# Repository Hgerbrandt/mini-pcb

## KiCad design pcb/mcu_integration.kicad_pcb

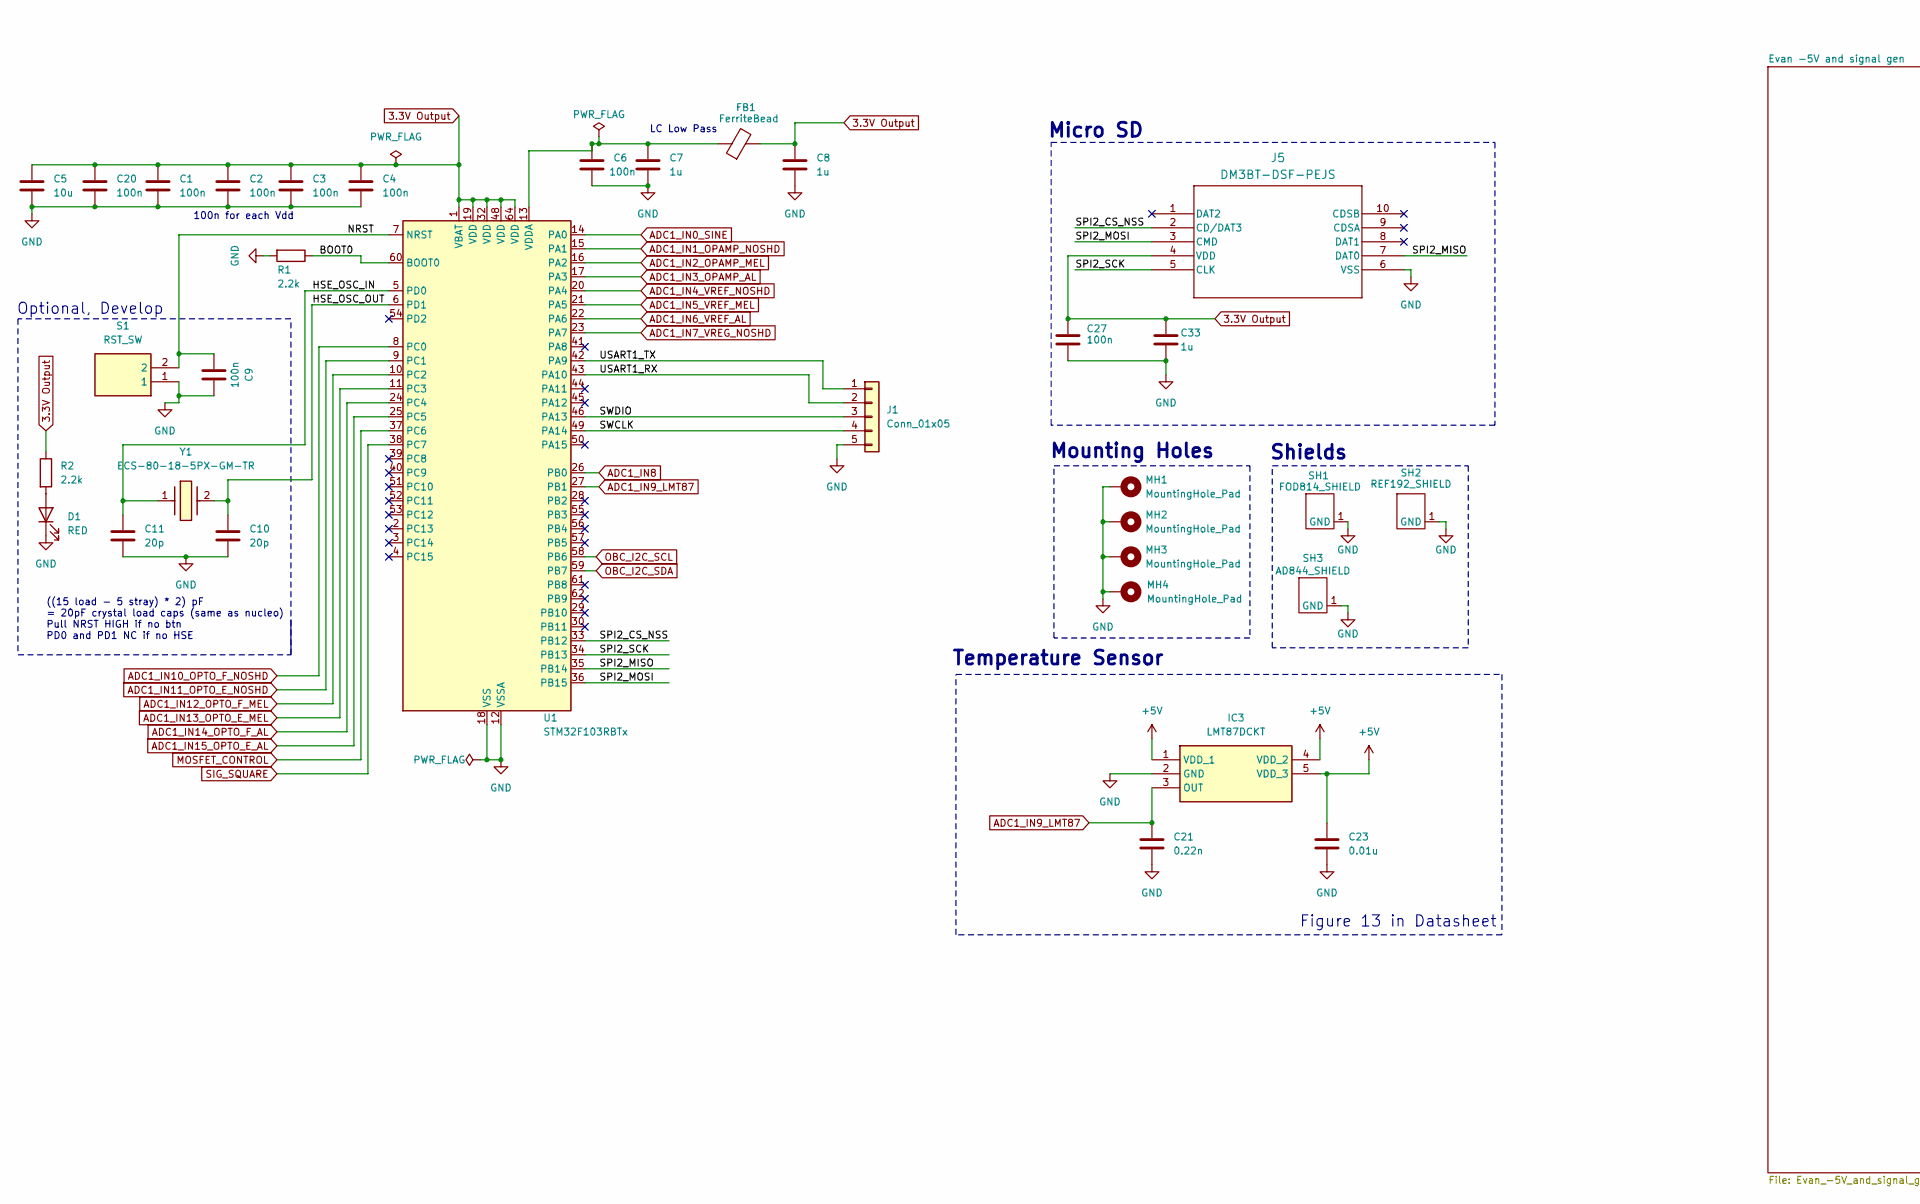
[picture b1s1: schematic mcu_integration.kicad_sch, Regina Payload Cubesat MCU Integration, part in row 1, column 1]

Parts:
C1, C2, C3, C4, C6, C9, C20, C27: 100n; C_0402_1005Metric
C5: 10u; C_0603_1608Metric
C7, C8, C33: 1u; C_0402_1005Metric
C10, C11: 20p; C_0402_1005Metric
C21: 0.22n; C_0402_1005Metric
C23: 0.01u; C_0402_1005Metric
D1: RED; LED_0603_1608Metric
FB1: FerriteBead; L_0603_1608Metric
IC3: LMT87DCKT; SOT65P210X110-5N; Mouser Part Number 595-LMT87DCKT
J1: Conn_01x05; PinHeader_1x05_P2.54mm_Vertical
J5: DM3BT-DSF-PEJS; DM3BT_DSF_PEJS
MH1, MH2, MH3, MH4: MountingHole_Pad; MountingHole_3.18mm_6.35mm_Pad
R1, R2: 2.2k; R_0402_1005Metric
S1: RST_SW; 95C04A3GWRT; Mouser Part Number 706-95C04A3GWRT
SH1: FOD814_SHIELD; FOD814 Shield
SH2: REF192_SHIELD; REF192 Shield
SH3: AD844_SHIELD; AD844 Shield
U1: STM32F103RBTx; LQFP-64_10x10mm_P0.5mm
Y1: ECS-80-18-5PX-GM-TR; ECS80185PXGMTR; Mouser Part Number 520-80-18-5PX-GM-TR

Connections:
3.3V Output: C1.1, C2.1, C3.1, C4.1, C5.1, C8.1, C20.1, C27.1, C33.1, FB1.2, J5.4 (VDD), R2.1, U1.1 (VBAT), U1.19 (VDD), U1.32 (VDD), U1.48 (VDD), U1.64 (VDD); also elsewhere on the board
+5V: C23.1, IC3.1 (VDD_1), IC3.4 (VDD_2), IC3.5 (VDD_3); also elsewhere on the board
/BOOT0: R1.1, U1.60 (BOOT0)
/HSE_OSC_IN: C11.1, U1.5 (PD0), Y1.1
/HSE_OSC_OUT: C10.1, U1.6 (PD1), Y1.2
/NRST: C9.2, S1.2, U1.7 (NRST)
/SPI2_CS_NSS: J5.2 (CD/DAT3), U1.33 (PB12)
/SPI2_MISO: J5.7 (DAT0), U1.35 (PB14)
/SPI2_MOSI: J5.3 (CMD), U1.36 (PB15)
/SPI2_SCK: J5.5 (CLK), U1.34 (PB13)
/SWCLK: J1.4, U1.49 (PA14)
/SWDIO: J1.3, U1.46 (PA13)
/USART1_RX: J1.2, U1.43 (PA10)
/USART1_TX: J1.1, U1.42 (PA9)
ADC1_IN0_SINE: U1.14 (PA0); also elsewhere on the board
ADC1_IN1_OPAMP_NOSHD: U1.15 (PA1)
ADC1_IN2_OPAMP_MEL: U1.16 (PA2)
ADC1_IN3_OPAMP_AL: U1.17 (PA3); also elsewhere on the board
ADC1_IN4_VREF_NOSHD: U1.20 (PA4)
ADC1_IN5_VREF_MEL: U1.21 (PA5)
ADC1_IN6_VREF_AL: U1.22 (PA6); also elsewhere on the board
ADC1_IN7_VREG_NOSHD: U1.23 (PA7)
ADC1_IN8: U1.26 (PB0)
ADC1_IN9_LMT87: C21.1, IC3.3 (OUT), U1.27 (PB1)
ADC1_IN10_OPTO_F_NOSHD: U1.8 (PC0)
ADC1_IN11_OPTO_E_NOSHD: U1.9 (PC1)
ADC1_IN12_OPTO_F_MEL: U1.10 (PC2)
ADC1_IN13_OPTO_E_MEL: U1.11 (PC3)
ADC1_IN14_OPTO_F_AL: U1.24 (PC4); also elsewhere on the board
ADC1_IN15_OPTO_E_AL: U1.25 (PC5); also elsewhere on the board
GND: C1.2, C2.2, C3.2, C4.2, C5.2, C6.2, C7.2, C8.2, C9.1, C10.2, C11.2, C20.2, C21.2, C23.2, C27.2, C33.2, D1.1 (K), IC3.2 (GND), J1.5, J5.6 (VSS), MH1.1, MH2.1, MH3.1, MH4.1, R1.2, S1.1, SH1.1 (GND), SH2.1 (GND), SH3.1 (GND), U1.12 (VSSA), U1.18 (VSS), U1.31 (VSS), U1.47 (VSS), U1.63 (VSS); also elsewhere on the board
MOSFET_CONTROL: U1.37 (PC6)
unnamed: D1.2 (A), R2.2
unnamed: C6.1, C7.1, FB1.1, U1.13 (VDDA)
OBC_I2C_SCL: U1.58 (PB6); also elsewhere on the board
OBC_I2C_SDA: U1.59 (PB7); also elsewhere on the board
SIG_SQUARE: U1.38 (PC7); also elsewhere on the board

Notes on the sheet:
((15 load - 5 stray) * 2) pF = 20pF crystal load caps (same as nucleo) Pull NRST HIGH if no btn PD0 and PD1 NC if no HSE
Mounting Holes
Micro SD
Optional, Develop
Temperature Sensor
100n for each Vdd
Shields
Figure 13 in Datasheet
LC Low Pass

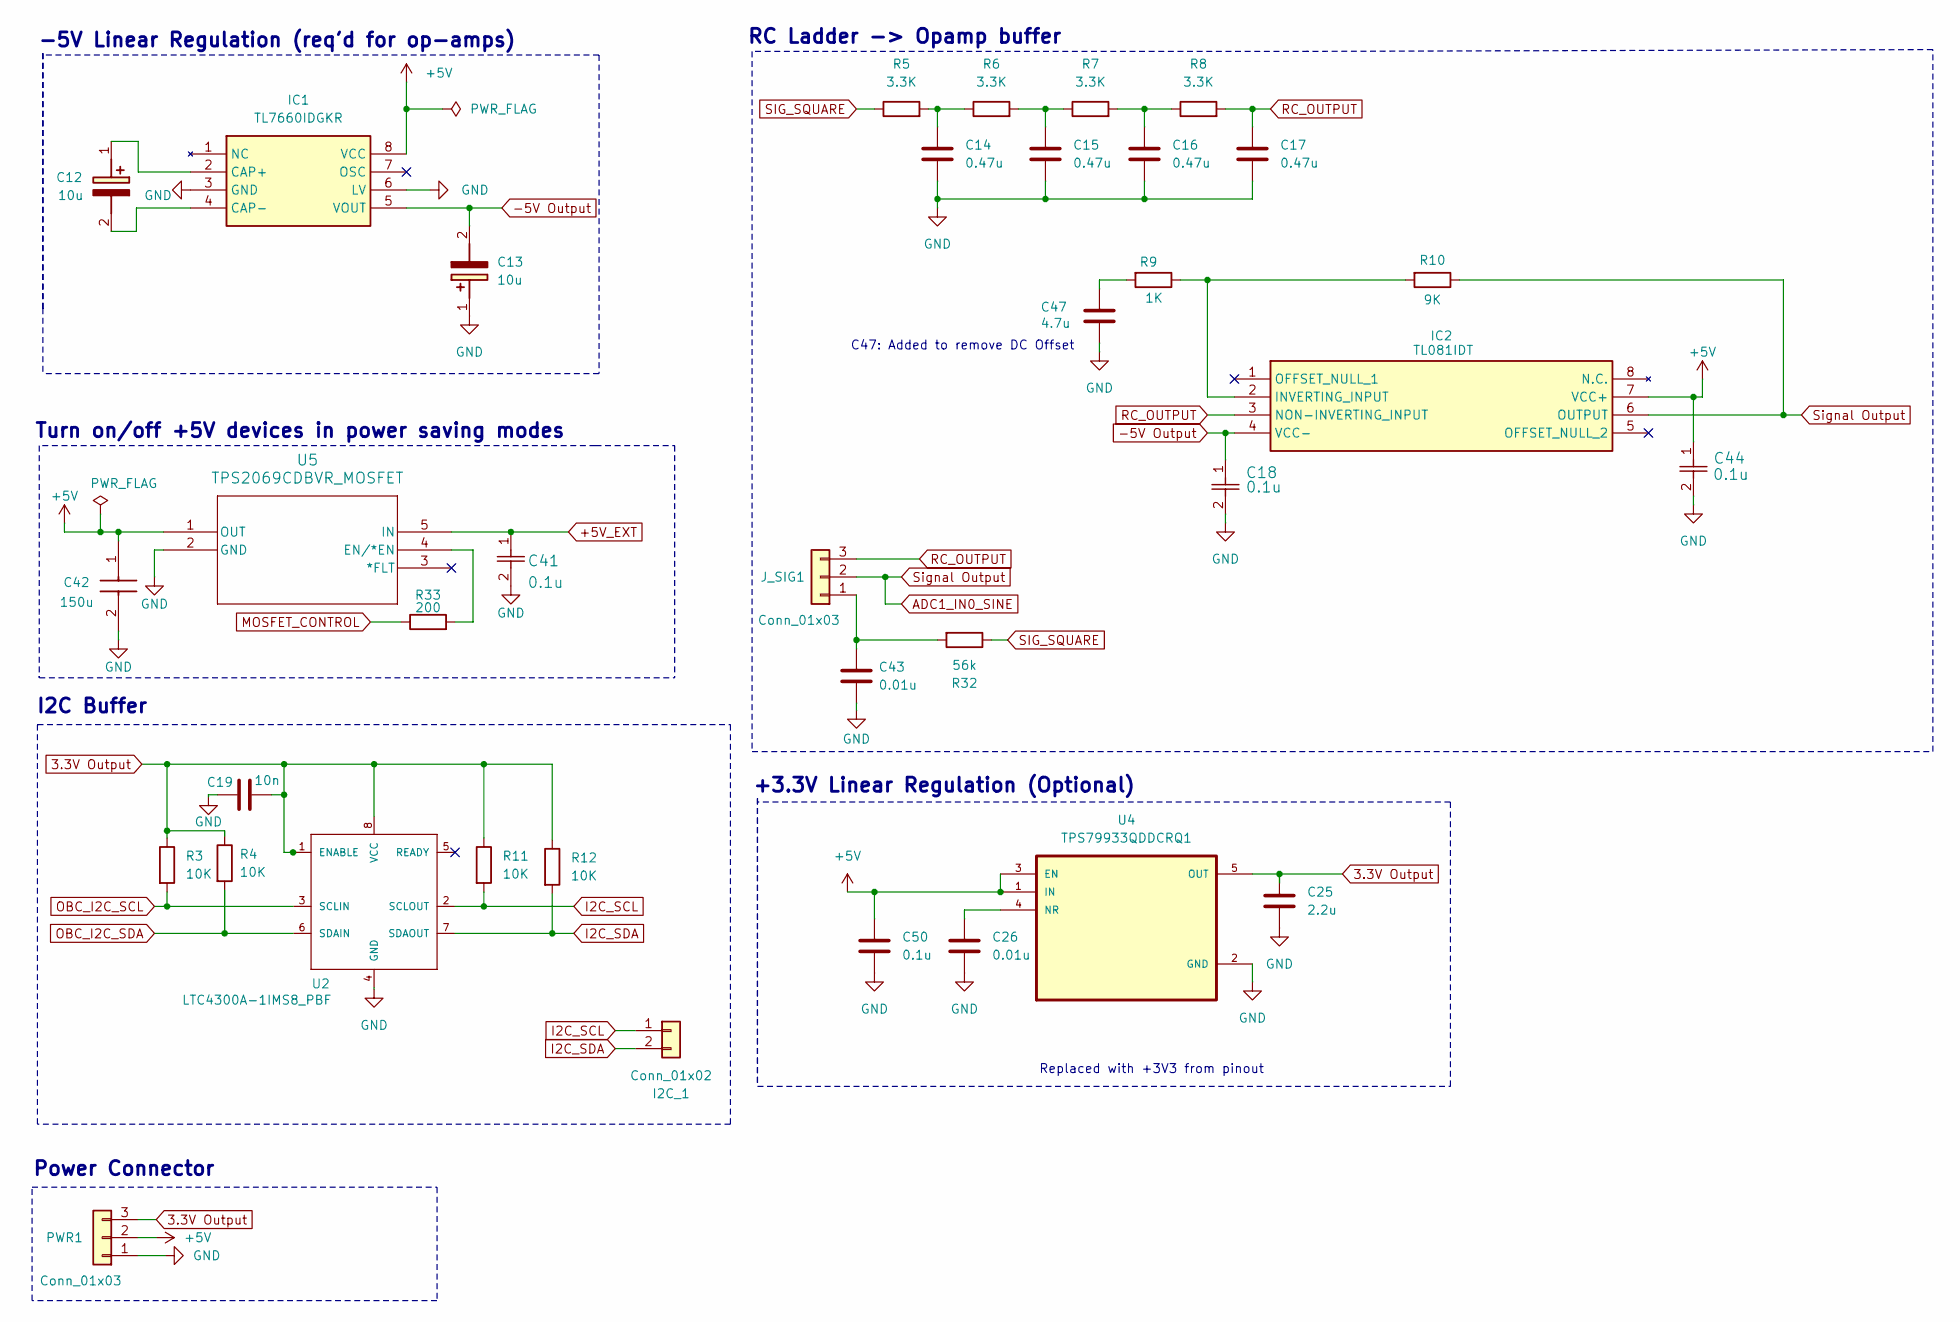
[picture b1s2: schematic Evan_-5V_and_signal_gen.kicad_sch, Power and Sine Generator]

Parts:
C12, C13: 10u; C_0805_2012Metric; Mouser Part Number 80-T495D106K035
C14, C15, C16, C17: 0.47u; C_0402_1005Metric
C18: 0.1u; C_0805_2012Metric
C19: 10n; C_0402_1005Metric
C25: 2.2u; C_0402_1005Metric
C26, C43: 0.01u; C_0402_1005Metric
C41, C44: 0.1u; CAPC220145_88N_KEM-0.1u
C42: 150u; CAPC3225X280N_150U; Mouser Part Number 187-CL32A157MQVNNNE
C47: 4.7u; C_0402_1005Metric
C50: 0.1u; C_0402_1005Metric
I2C_1: Conn_01x02; PinHeader_1x02_P2.54mm_Vertical
IC1: TL7660IDGKR; SOP65P490X110-8N-actual; Mouser Part Number 595-TL7660IDGKR
IC2: TL081IDT; SOIC127P600X175-8N; Mouser Part Number 511-TL081IDT
J_SIG1: Conn_01x03; PinHeader_1x03_P2.54mm_Vertical
PWR1: Conn_01x03; PinHeader_1x03_P2.54mm_Vertical
R3, R4, R11, R12: 10K; R_0402_1005Metric
R5, R6, R7, R8: 3.3K; R_0402_1005Metric
R9: 1K; R_0402_1005Metric
R10: 9K; R_0402_1005Metric
R32: 56k; R_0402_1005Metric
R33: 200; R_0402_1005Metric
U2: LTC4300A-1IMS8_PBF; MANUFACTURER_PART_NUMBER ltc4300a1ims8
U4: TPS79933QDDCRQ1; SOT95P280X110-5N
U5: TPS2069CDBVR_MOSFET; DBV5_TEX_MF

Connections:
3.3V Output: C19.2, C25.1, PWR1.3, R3.1, R4.1, R11.1, R12.1, U2.1 (ENABLE), U2.8 (VCC), U4.5 (OUT); also elsewhere on the board
+5V: C42.1, C44.1, C50.1, IC1.8 (VCC), IC2.7 (VCC+), PWR1.2, U4.1 (IN), U4.3 (EN), U5.1 (OUT); also elsewhere on the board
-5V Output: C13.2 (-), C18.1, IC1.5 (VOUT), IC2.4 (VCC-); also elsewhere on the board
ADC1_IN0_SINE: IC2.6 (OUTPUT), J_SIG1.2, R10.1; also elsewhere on the board
GND: C13.1 (+), C14.2, C15.2, C16.2, C17.2, C18.2, C19.1, C25.2, C26.2, C41.2, C42.2, C43.1, C44.2, C47.2, C50.2, IC1.3 (GND), IC1.6 (LV), PWR1.1, U2.4 (GND), U4.2 (GND), U5.2 (GND); also elsewhere on the board
I2C_SCL: I2C_1.1, R11.2, U2.2 (SCLOUT)
I2C_SDA: I2C_1.2, R12.2, U2.7 (SDAOUT)
unnamed: C12.1 (+), IC1.2 (CAP+)
unnamed: C12.2 (-), IC1.4 (CAP-)
unnamed: C14.1, R5.2, R6.1
unnamed: C15.1, R6.2, R7.1
unnamed: C16.1, R7.2, R8.1
unnamed: C41.1, U5.5 (IN)
unnamed: C47.1, R9.2
unnamed: IC2.2 (INVERTING_INPUT), R9.1, R10.2
unnamed: C43.2, J_SIG1.1, R32.2
unnamed: R33.2, U5.4 (EN/*EN)
unnamed: C26.1, U4.4 (NR)
OBC_I2C_SCL: R3.2, U2.3 (SCLIN); also elsewhere on the board
OBC_I2C_SDA: R4.2, U2.6 (SDAIN); also elsewhere on the board
RC_OUTPUT: C17.1, IC2.3 (NON-INVERTING_INPUT), J_SIG1.3, R8.2
SIG_SQUARE: R5.1, R32.1; also elsewhere on the board

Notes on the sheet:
+3.3V Linear Regulation (Optional)
-5V Linear Regulation (req'd for op-amps)
C47: Added to remove DC Offset
Power Connector
RC Ladder -> Opamp buffer
I2C Buffer
Turn on/off +5V devices in power saving modes
Replaced with +3V3 from pinout

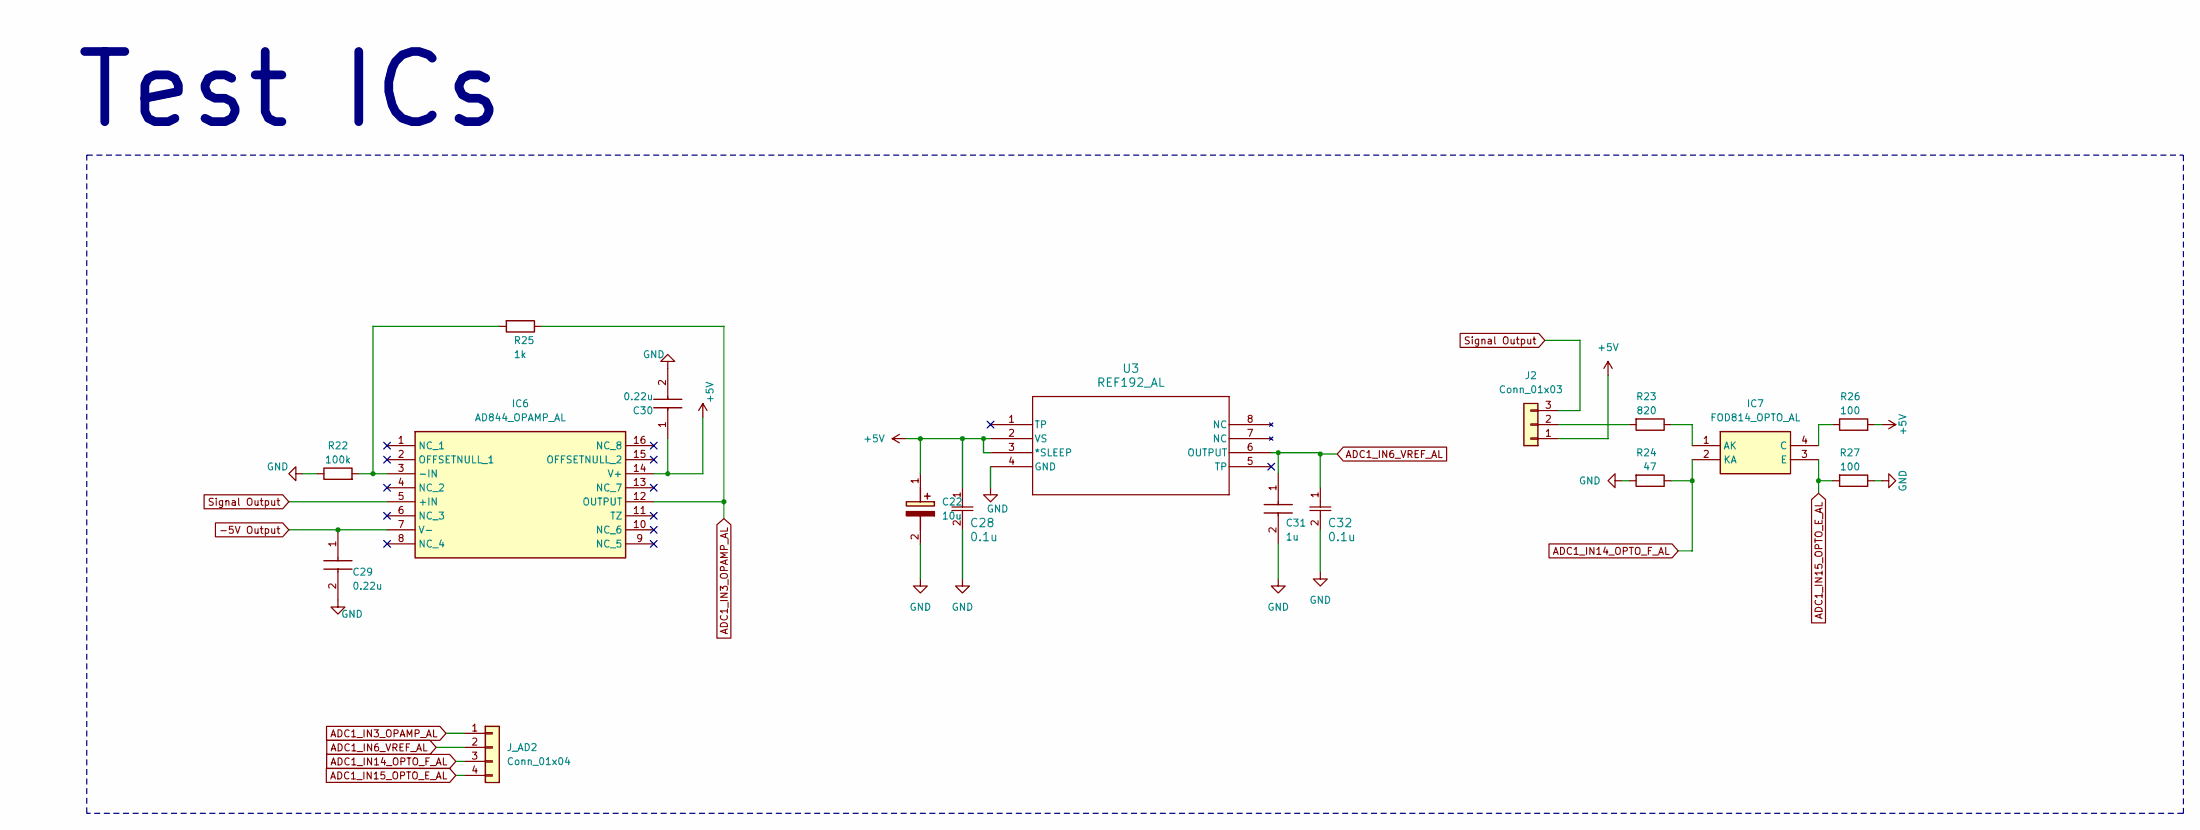
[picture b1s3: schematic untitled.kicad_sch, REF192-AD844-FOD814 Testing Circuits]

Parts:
C22: 10u; C_0805_2012Metric; Mouser Part Number 80-T495D106K035
C28, C32: 0.1u; CAPC220145_88N_KEM-0.1u
C29, C30: 0.22u; C0805-0.22u; Manufacturer_Part_Number C0805C224M5VACTU
C31: 1u; C0805-1u; Mouser Part Number 80-C0805C105Z5VACTU
IC6: AD844_OPAMP_AL; SOIC127P1032X265-16N-AD844; Mouser Part Number 584-AD844JRZ-16-R7
IC7: FOD814_OPTO_AL; SOP254P1016X385-4N-FOD; Mouser Part Number 512-FOD814SD
J2: Conn_01x03; PinHeader_1x03_P2.54mm_Vertical
J_AD2: Conn_01x04; PinHeader_1x04_P2.54mm_Vertical
R22: 100k; R_0402_1005Metric
R23: 820; R_0402_1005Metric
R24: 47; R_0402_1005Metric
R25: 1k; R_0402_1005Metric
R26, R27: 100; R_0402_1005Metric
U3: REF192_AL; R_8_ADI-REF

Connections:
+5V: C22.1 (+), C28.1, C30.1, IC6.14 (V+), J2.1, R26.2, U3.2 (VS), U3.3 (*SLEEP); also elsewhere on the board
-5V Output: C29.1, IC6.7 (V-); also elsewhere on the board
ADC1_IN0_SINE: IC6.5 (+IN), J2.3; also elsewhere on the board
ADC1_IN3_OPAMP_AL: IC6.12 (OUTPUT), J_AD2.1, R25.1; also elsewhere on the board
ADC1_IN6_VREF_AL: C31.1, C32.1, J_AD2.2, U3.6 (OUTPUT); also elsewhere on the board
ADC1_IN14_OPTO_F_AL: IC7.2 (KA), J_AD2.3, R24.1; also elsewhere on the board
ADC1_IN15_OPTO_E_AL: IC7.3 (E), J_AD2.4, R27.2; also elsewhere on the board
GND: C22.2 (-), C28.2, C29.2, C30.2, C31.2, C32.2, R22.1, R24.2, R27.1, U3.4 (GND); also elsewhere on the board
unnamed: IC6.3 (-IN), R22.2, R25.2
unnamed: IC7.1 (AK), R23.1
unnamed: IC7.4 (C), R26.1
unnamed: J2.2, R23.2

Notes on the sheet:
Test ICs

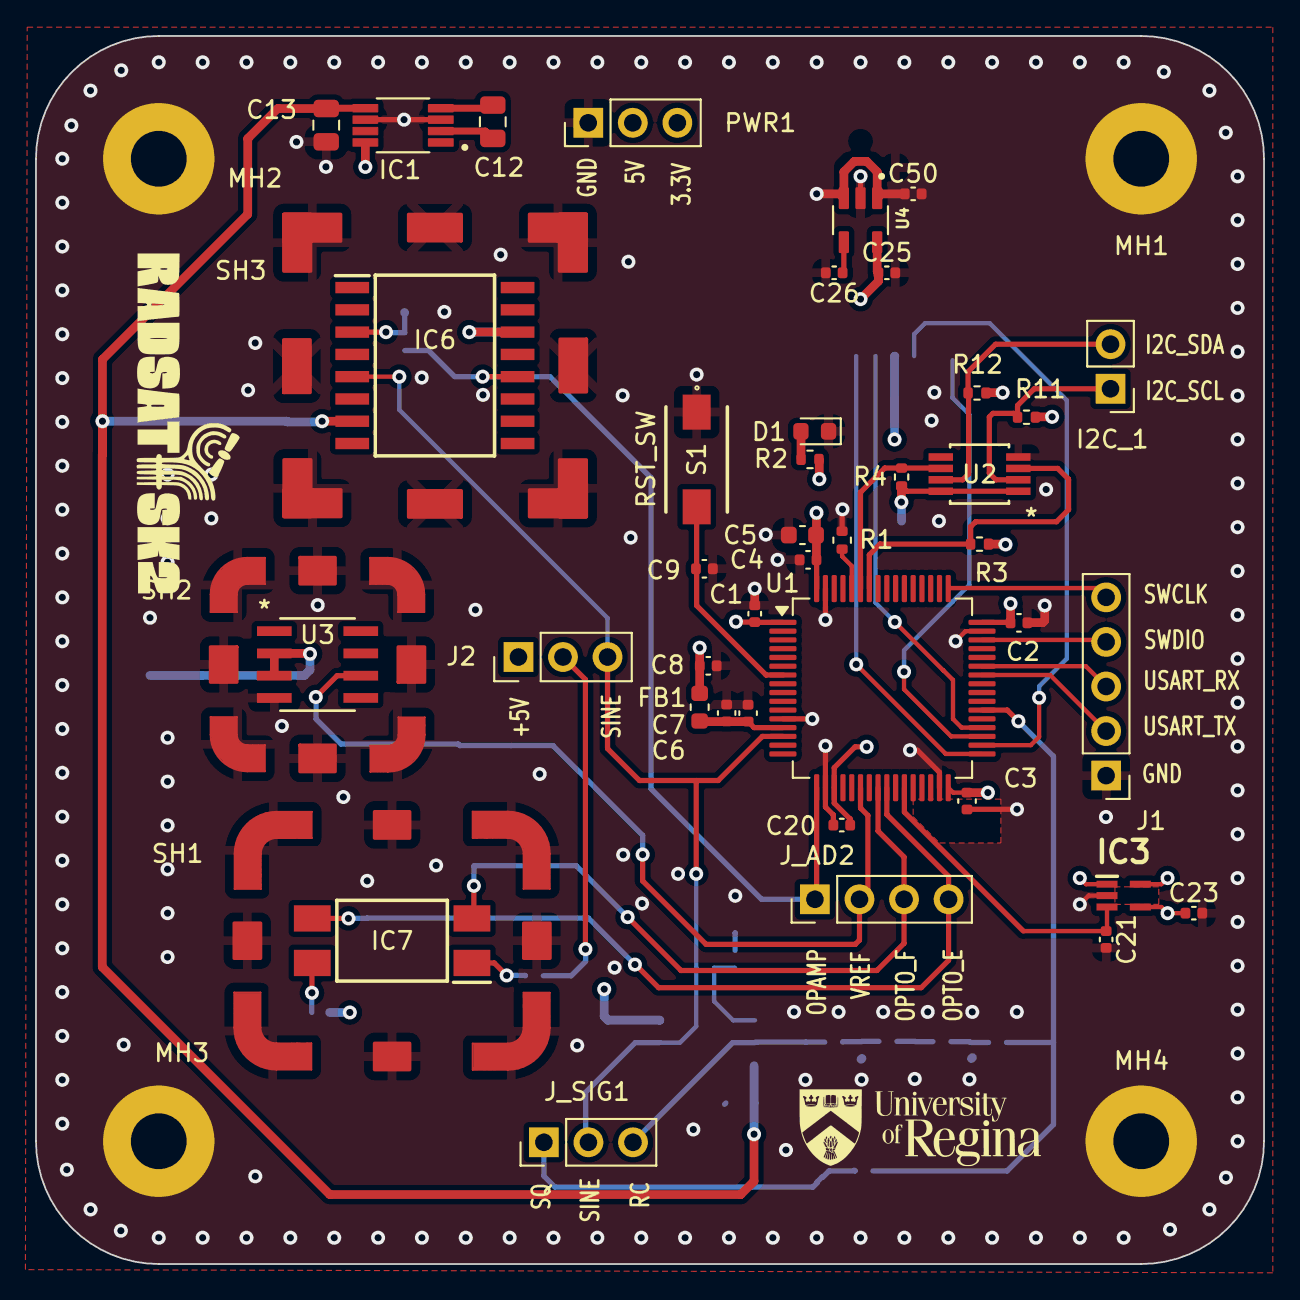
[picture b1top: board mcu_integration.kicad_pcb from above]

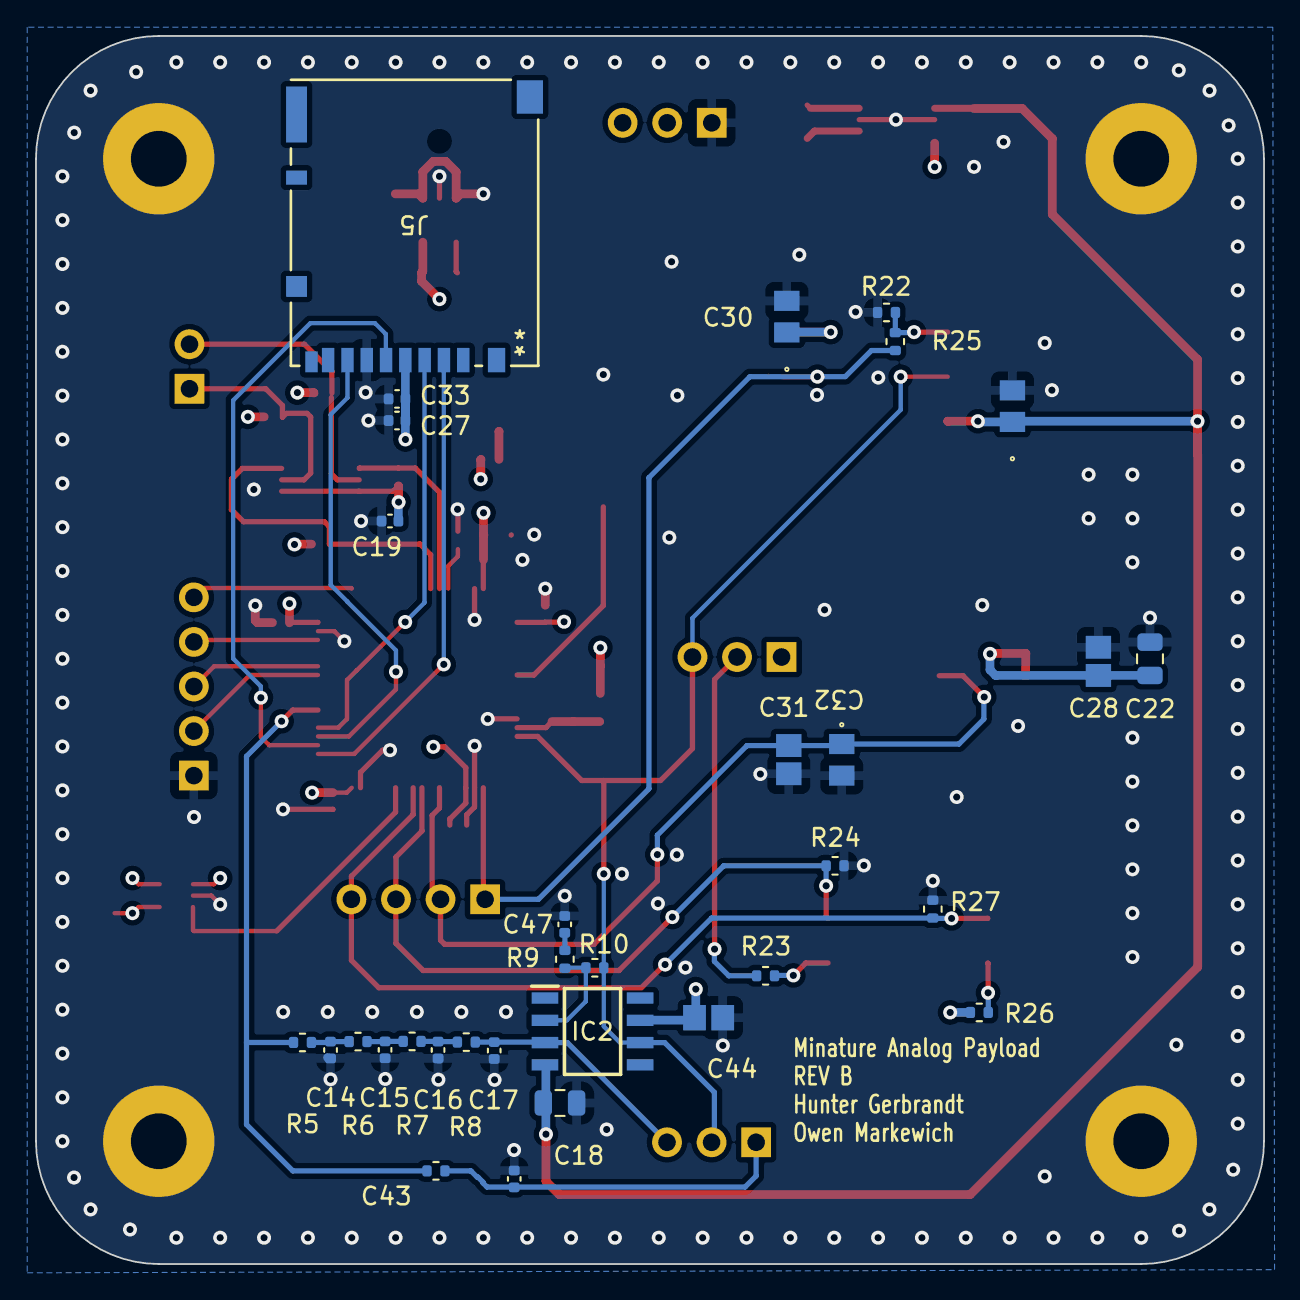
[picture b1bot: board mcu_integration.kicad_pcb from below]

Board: 4 copper layers, 70.0 x 70.0 mm, 79 parts (36 on the bottom side), 41 nets.

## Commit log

2025-03-23 Added PCB Files
2025-03-30 Restructured PCB
2025-03-30 Arranged components to fit board
2025-03-31 Added two pin connector, routed all connections
2025-03-31 Added I2C Connector
2025-04-06 Increased board size from 5x5 to 7x7
2025-05-11 Added reset button & LED, fixed SD card overhang
2025-05-18 Added non-inverting amplifier
2025-05-19 Changed spacing between test ICs
2025-05-25 changed 5 volt nets from 0.25mm to 0.5mm
2025-05-25 Fixed pin labels
2025-05-25 Ran DFM and made adjustments accordingly
2025-06-27 changed footprints and layout
2025-08-17 Added Shields
2025-08-24 Adjusted Silkscreen
2025-08-31 Fixed Footprints
    -Added Solder Mask
    -Symbol Pin Numbers
2025-11-23 Added capacitor to op amp circuit
2025-12-08 Added switchable input for opto-coupler
2026-01-11 Changed IC test orientation
2026-01-16 Thermal Reliefs for Shields
2026-02-04 Replaced LM35 temp sensor with LMT87
2026-03-15 Added 3V3 linear voltage regulator
2026-06-21 Updated BOM
